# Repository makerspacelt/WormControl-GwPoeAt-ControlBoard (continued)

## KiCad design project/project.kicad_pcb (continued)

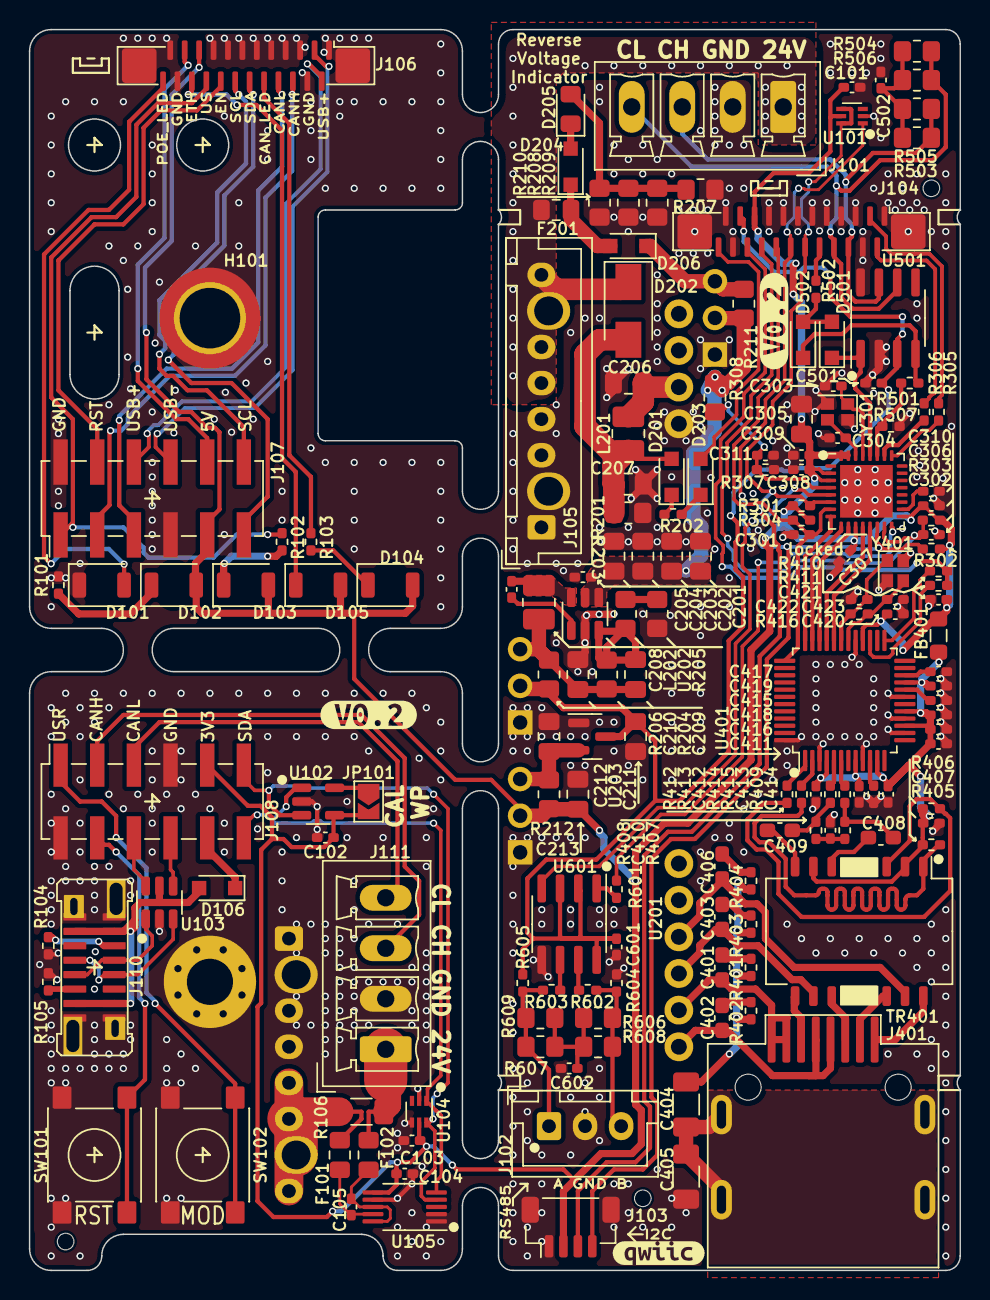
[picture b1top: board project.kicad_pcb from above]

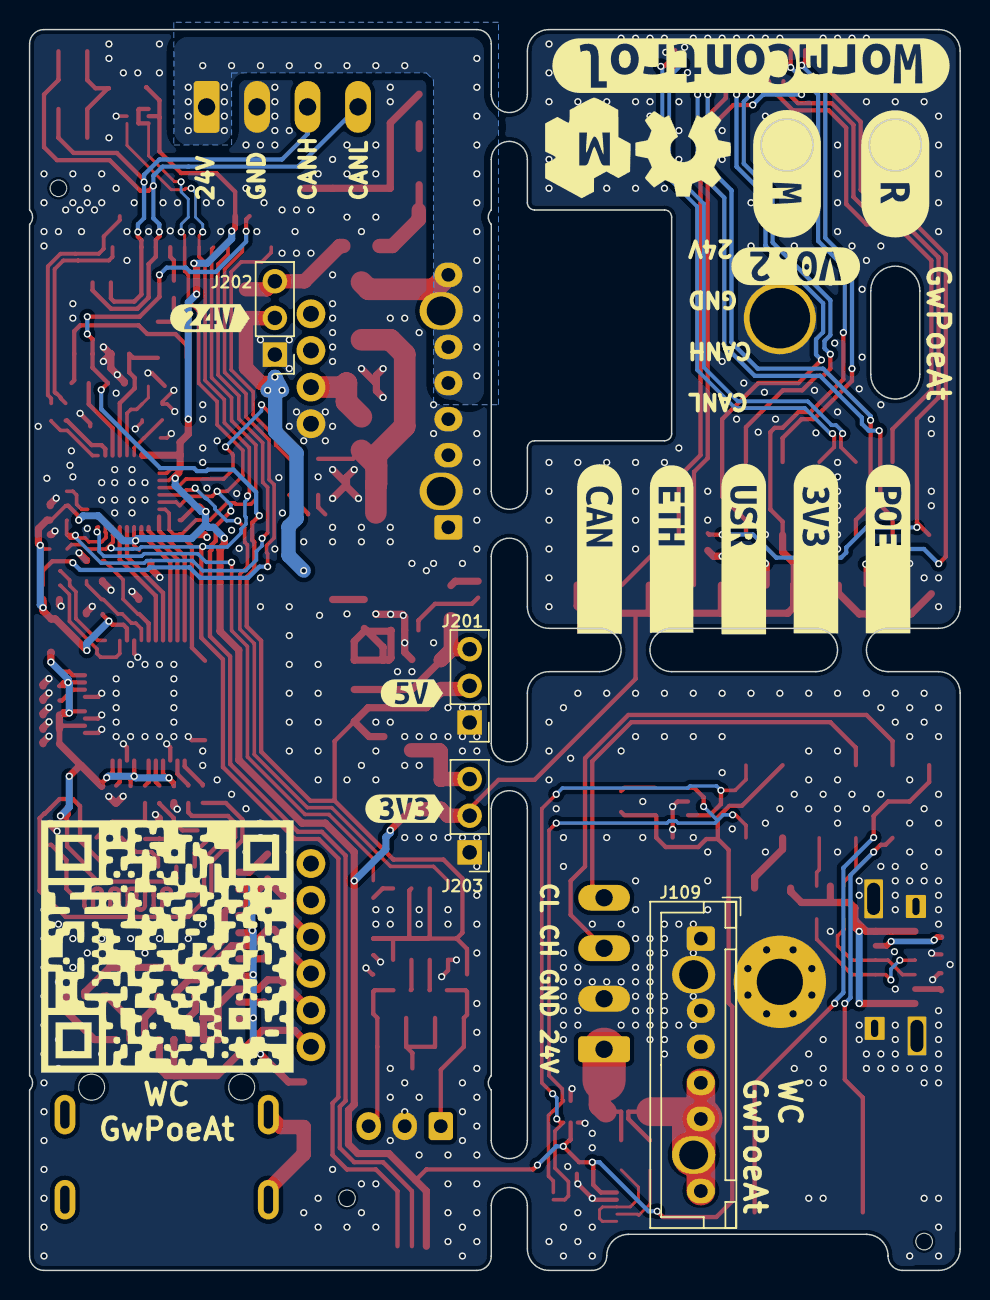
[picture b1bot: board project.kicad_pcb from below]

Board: 4 copper layers, 64.5 x 86.0 mm, 186 parts (18 on the bottom side), 121 nets.

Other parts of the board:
kibuzzard-6A7A3E96: G***; kibuzzard-6A7A3E96
kibuzzard-6A7A3EB1: G***; kibuzzard-6A7A3EB1
kibuzzard-6A7A3F37: G***; kibuzzard-6A7A3F37
kibuzzard-68F6C7D9: G***; kibuzzard-68F6C7D9
kibuzzard-68F6C776: G***; kibuzzard-68F6C776
kibuzzard-68F6C793: G***; kibuzzard-68F6C793
kibuzzard-69A9CC91: G***; kibuzzard-69A9CC91
kibuzzard-69AA2F96: G***; kibuzzard-69AA2F96
kibuzzard-69AEA4F2: G***; kibuzzard-69AEA4F2
kibuzzard-69AFA227: G***; kibuzzard-69AFA227
kibuzzard-69AFDF3E: G***; kibuzzard-69AFDF3E
kibuzzard-69AFDF44: G***; kibuzzard-69AFDF44
kibuzzard-69938F5C: G***; kibuzzard-69938F5C
kibuzzard-69938F55: G***; kibuzzard-69938F55
kibuzzard-69938F62: G***; kibuzzard-69938F62
locked: esp32-C3FH4X; QFN-32-1EP_5x5mm_P0.5mm_EP3.65x3.65mm

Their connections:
3V3: locked.2 (VDD3P3), locked.3 (VDD3P3), locked.11 (VDD3P3_RTC), locked.17 (VDD3P3_CPU), locked.31 (VDDA), locked.32 (VDDA); also elsewhere on the board
/CAN_RX: locked.27 (IO20/RX); also elsewhere on the board
/CAN_TX: locked.28 (IO21/TX); also elsewhere on the board
/ETH/CLK: locked.12 (IO6/SPI_MOSI); also elsewhere on the board
/ETH/CS: locked.13 (IO7/SPI_SS); also elsewhere on the board
/ETH/INT: locked.8 (IO3/ADC1_3); also elsewhere on the board
/ETH/MISO: locked.10 (IO5/ADC2/SPI_MISO); also elsewhere on the board
/ETH/MOSI: locked.9 (IO4/ADC1_4/SPI_SCK); also elsewhere on the board
/RS485_RX: locked.16 (IO10); also elsewhere on the board
/RS485_TX: locked.5 (IO1/ADC1_1); also elsewhere on the board
/uC/ADC: locked.4 (IO0/ADC1_0); also elsewhere on the board
/uC/USB_D_N: locked.25 (IO18/USB_N); also elsewhere on the board
/uC/USB_D_P: locked.26 (IO19/USB_P); also elsewhere on the board
/uC/VDD_SPI: locked.18 (VDD_SPI); also elsewhere on the board
/uC/XTAL_N: locked.29 (XTAL_N); also elsewhere on the board
/uC/XTAL_P: locked.30 (XTAL_P); also elsewhere on the board
EN: locked.7 (CHIP_EN); also elsewhere on the board
GND: locked.33 (GND); also elsewhere on the board
SCL: locked.14 (IO8/BOOT); also elsewhere on the board
SDA: locked.6 (IO2/BOOT/ADC1_2); also elsewhere on the board
USR_LED: locked.15 (IO9/BOOT); also elsewhere on the board

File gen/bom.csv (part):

"Row","Description","Part","References","Value","Footprint","Quantity Per PCB","Status","Datasheet","lcsc#","jlc-part-type","alt#"
"1","Heatsink","Heatsink","BOM101,BOM102","1x4 screw plug","~","2"," ","https://www.lcsc.com/datasheet/C7603442.pdf","C7603442","E+",""
"2","Unpolarized capacitor","C","C303,C304,C422,C423","10p","C_0402_1005Metric_Pad0.74x0.62mm_HandSolder","4"," ","~","C32949","B+",""
"3","Unpolarized capacitor","C","C209","100p","C_0805_2012Metric_Pad1.18x1.45mm_HandSolder","1"," ","~","C1790","B+",""
"4","Unpolarized capacitor","C","C408,C409","6n8","C_0603_1608Metric_Pad1.08x0.95mm_HandSolder","2"," ","~","C1631","B+",""
"5","Unpolarized capacitor","C","C101,C102,C103,C104,C105,C301,C302,C306,C307,C308,C309,C310,C311,C407,C410,C412,C413,C414,C416,C417,C418,C419,C420,C501,C502,C601,C602","100n","C_0402_1005Metric_Pad0.74x0.62mm_HandSolder","27"," ","~","C1525","B+",""
"6","Unpolarized capacitor","C","C415","4u7","C_0402_1005Metric_Pad0.74x0.62mm_HandSolder","1"," ","~","C23733","B+",""
"7","Unpolarized capacitor","C","C205,C208","100n/50V","C_0402_1005Metric_Pad0.74x0.62mm_HandSolder","2"," ","~","C307331","B+",""
"8","Unpolarized capacitor","C","C201,C202,C203,C204,C206,C207,C210","10u/50v","C_0805_2012Metric_Pad1.18x1.45mm_HandSolder","7"," ","~","C440198","B+",""
"9","Unpolarized capacitor","C","C411,C421","10u/6v3","C_0402_1005Metric_Pad0.74x0.62mm_HandSolder","2"," ","~","C15525","B+",""
"10","Unpolarized capacitor","C","C404","1n/2kv","C_1206_3216Metric_Pad1.33x1.80mm_HandSolder","1"," ","~","C9196","B+",""
"11","Unpolarized capacitor","C","C401,C402,C403,C406","22n/100v","C_0603_1608Metric_Pad1.08x0.95mm_HandSolder","4"," ","~","C22374871","E+",""
"12","Unpolarized capacitor","C","C211,C305","22u/25v","C_0805_2012Metric_Pad1.18x1.45mm_HandSolder","2"," ","~","C45783","B+",""
"13","Unpolarized capacitor","C","C212,C213","47u/6V3","C_0805_2012Metric_Pad1.18x1.45mm_HandSolder","2"," ","~","C16780","B+",""
"14","Unpolarized capacitor","C","C405","4n7/2kv","C_1206_3216Metric_Pad1.33x1.80mm_HandSolder","1"," ","~","C41017","E+",""
"15","Zener diode","D_Zener","D203","6V8","D_SOD-323_HandSoldering","1"," ","https://www.lcsc.com/datasheet/C123062.pdf","C123062","E+",""
"16","Schottky diode","D_Schottky","D106,D201,D204,D206,D501,D502","B5819WS","D_SOD-323_HandSoldering","6"," ","https://www.lcsc.com/datasheet/C8598.pdf","C8598","B+",""
"17","Light emitting diode","LED","D205","BLUE","LED_0805_2012Metric_Pad1.15x1.40mm_HandSolder","1"," ","https://www.lcsc.com/datasheet/C2297.pdf","C2297","B+",""
"18","Light emitting diode","LED","D101,D102,D103,D104,D105","RED","LED_1206_3216Metric_ReverseMount","5"," ","https://www.lcsc.com/datasheet/C5356080.pdf","C5356080","E+",""
"19","Schottky diode","D_Schottky","D202","SS34","D_SMA","1"," ","https://www.lcsc.com/datasheet/C8678.pdf","C8678","B+",""
"20","Resettable fuse, polymeric positive temperature coefficient","Polyfuse","F101,F102","10mA","Fuse_0805_2012Metric_Pad1.15x1.40mm_HandSolder","2"," ","https://www.lcsc.com/datasheet/C7472543.pdf","C7472543","E+",""
"21","Resettable fuse, polymeric positive temperature coefficient","Polyfuse","F201","250mA","Fuse_0805_2012Metric_Pad1.15x1.40mm_HandSolder","1"," ","https://www.lcsc.com/datasheet/C22378353.pdf","C22378353","E+",""
"22","Ferrite bead, small symbol","FerriteBead_Small","FB401","600R@100MHz","L_0805_2012Metric_Pad1.05x1.20mm_HandSolder","1"," ","~","C1017","B+",""
"23","Generic connector, single row, 01x03, script generated (kicad-library-utils/schlib/autogen/connector/)","Conn_01x03","J201,J202,J203","5V","PinHeader_1x03_P2.54mm_Vertical","3"," ","~","","-",""
"24","Generic screw terminal, single row, 01x04, script generated (kicad-library-utils/schlib/autogen/connector/)","Screw_Terminal_01x04","J101,J111","BUS","PhoenixContact_MCV_1,5_4-G-3.5_1x04_P3.50mm_Vertical","2"," ","https://www.lcsc.com/datasheet/C880556.pdf","C880556","E+",""
"25","Generic connector, single row, 01x08, script generated (kicad-library-utils/schlib/autogen/connector/)","Conn_01x08","J105,J109","Bot","JST_XH_B8B-XH-A_1x08_P2.50mm_Vertical","2"," ","~","","???",""
"26","Generic connectable mounting pin connector, single row, 01x24, script generated (kicad-library-utils/schlib/autogen/connector/)","Conn_01x24_MountingPin","J104,J106","FFC","AFC11-S24ICC-00","2"," ","https://www.lcsc.com/datasheet/C11075.pdf","C11075","E+",""
"27","Generic connector, single row, 01x12, script generated (kicad-library-utils/schlib/autogen/connector/)","Conn_01x12","J108","Mid","PinSocket_2x06_P2.54mm_Vertical_SMD","1"," ","https://www.lcsc.com/datasheet/C3975151.pdf","C3975151","E+",""
"28","RJ connector, 8P8C (8 positions 8 connected), Shielded","RJ45_Shielded","J401","RJ45_Shielded","RJ45_FG_RJ-064-1","1"," ","https://www.lcsc.com/datasheet/C7205199.pdf","C7205199","E+",""
"29","Generic connector, single row, 01x12, script generated (kicad-library-utils/schlib/autogen/connector/)","Conn_01x12","J107","Top","PinHeader_2x06_P2.54mm_Vertical_SMD","1"," ","https://www.lcsc.com/datasheet/C5160780.pdf","C5160780","E+",""
"30","USB 2.0-only Type-C Receptacle connector","USB_C_Receptacle_USB2.0","J110","USB_C_Receptacle_USB2.0","USB_C_Receptacle_G-Switch_GT-USB-7082G","1"," ","https://www.lcsc.com/datasheet/C22383836.pdf","C22383836","E+",""
"31","Generic connectable mounting pin connector, single row, 01x04, script generated (kicad-library-utils/schlib/autogen/connector/)","Conn_01x04_MountingPin","J103","qwiic","JST_SH_BM04B-SRSS-TB_1x04-1MP_P1.00mm_Vertical","1"," ","https://www.lcsc.com/datasheet/C51940129.pdf","C51940129","E+",""
"32","Generic connector, single row, 01x03, script generated (kicad-library-utils/schlib/autogen/connector/)","Conn_01x03","J102","rs485","JST_XH_B3B-XH-A_1x03_P2.50mm_Vertical","1"," ","~","","???",""
"33","Inductor","L","L201,L202","3.3uH","L_1008_2520Metric_Pad1.43x2.20mm_HandSolder","2"," ","https://www.lcsc.com/datasheet/C5832373.pdf","C5832373","E+",""
"34","Resistor","R","R106","10m","R_1206_3216Metric_Pad1.30x1.75mm_HandSolder","1"," ","~","C7467248","E+",""
"35","Resistor","R","R206,R211,R212","0R1","R_0805_2012Metric_Pad1.20x1.40mm_HandSolder","3"," ","","C127687","E+",""
"36","Resistor","R","R602,R603","10R","R_0402_1005Metric_Pad0.72x0.64mm_HandSolder","2"," ","~","C25077","B+",""
"37","Resistor","R","R305,R306","22R","R_0402_1005Metric_Pad0.72x0.64mm_HandSolder","2"," ","~","C25092","B+",""
"38","Resistor","R","R412,R413,R414,R415","33R","R_0402_1005Metric_Pad0.72x0.64mm_HandSolder","4"," ","~","C25105","B+",""
"39","Resistor","R","R405,R406,R407,R408","49R9","R_0402_1005Metric_Pad0.72x0.64mm_HandSolder","4"," ","~","C25120","B+",""
"40","Resistor","R","R401,R402,R403,R404","75R","R_0402_1005Metric_Pad0.72x0.64mm_HandSolder","4"," ","~","C25133","ER+",""
"41","Resistor","R","R503,R504,R505,R506,R606,R607,R608,R609","120R","R_0805_2012Metric_Pad1.20x1.40mm_HandSolder","8"," ","~","C17437","B+",""
"42","Resistor","R","R501","1k5","R_0402_1005Metric_Pad0.72x0.64mm_HandSolder","1"," ","~","C4310","B+",""
"43","Resistor","R","R507","3k","R_0402_1005Metric_Pad0.72x0.64mm_HandSolder","1"," ","~","C17661","B+",""
"44","Resistor","R","R101,R102,R103,R104,R105,R301,R302,R303,R304,R307,R410,R502,R601","4k7","R_0402_1005Metric_Pad0.72x0.64mm_HandSolder","13"," ","~","C25900","B+",""
"45","Resistor","R","R207,R208,R209,R210","4k7","R_0805_2012Metric_Pad1.20x1.40mm_HandSolder","4"," ","~","C17673","B+",""
"46","Resistor","R","R201,R203,R205","10k","R_0805_2012Metric_Pad1.20x1.40mm_HandSolder","3"," ","~","C17414","B+",""
"47","Resistor","R","R604,R605","10k","R_0402_1005Metric_Pad0.72x0.64mm_HandSolder","2"," ","~","C25744","B+",""
"48","Resistor","R","R409,R411","12k4","R_0402_1005Metric_Pad0.72x0.64mm_HandSolder","2"," ","~","C11692","E+",""
"49","Resistor","R","R202","47k","R_0402_1005Metric_Pad0.72x0.64mm_HandSolder","1"," ","~","C25792","B+",""
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
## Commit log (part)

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2026-03-13 initial design
2026-03-15 updating poe psu model
2026-04-20 fix PSU FB and tmp102 pinout
